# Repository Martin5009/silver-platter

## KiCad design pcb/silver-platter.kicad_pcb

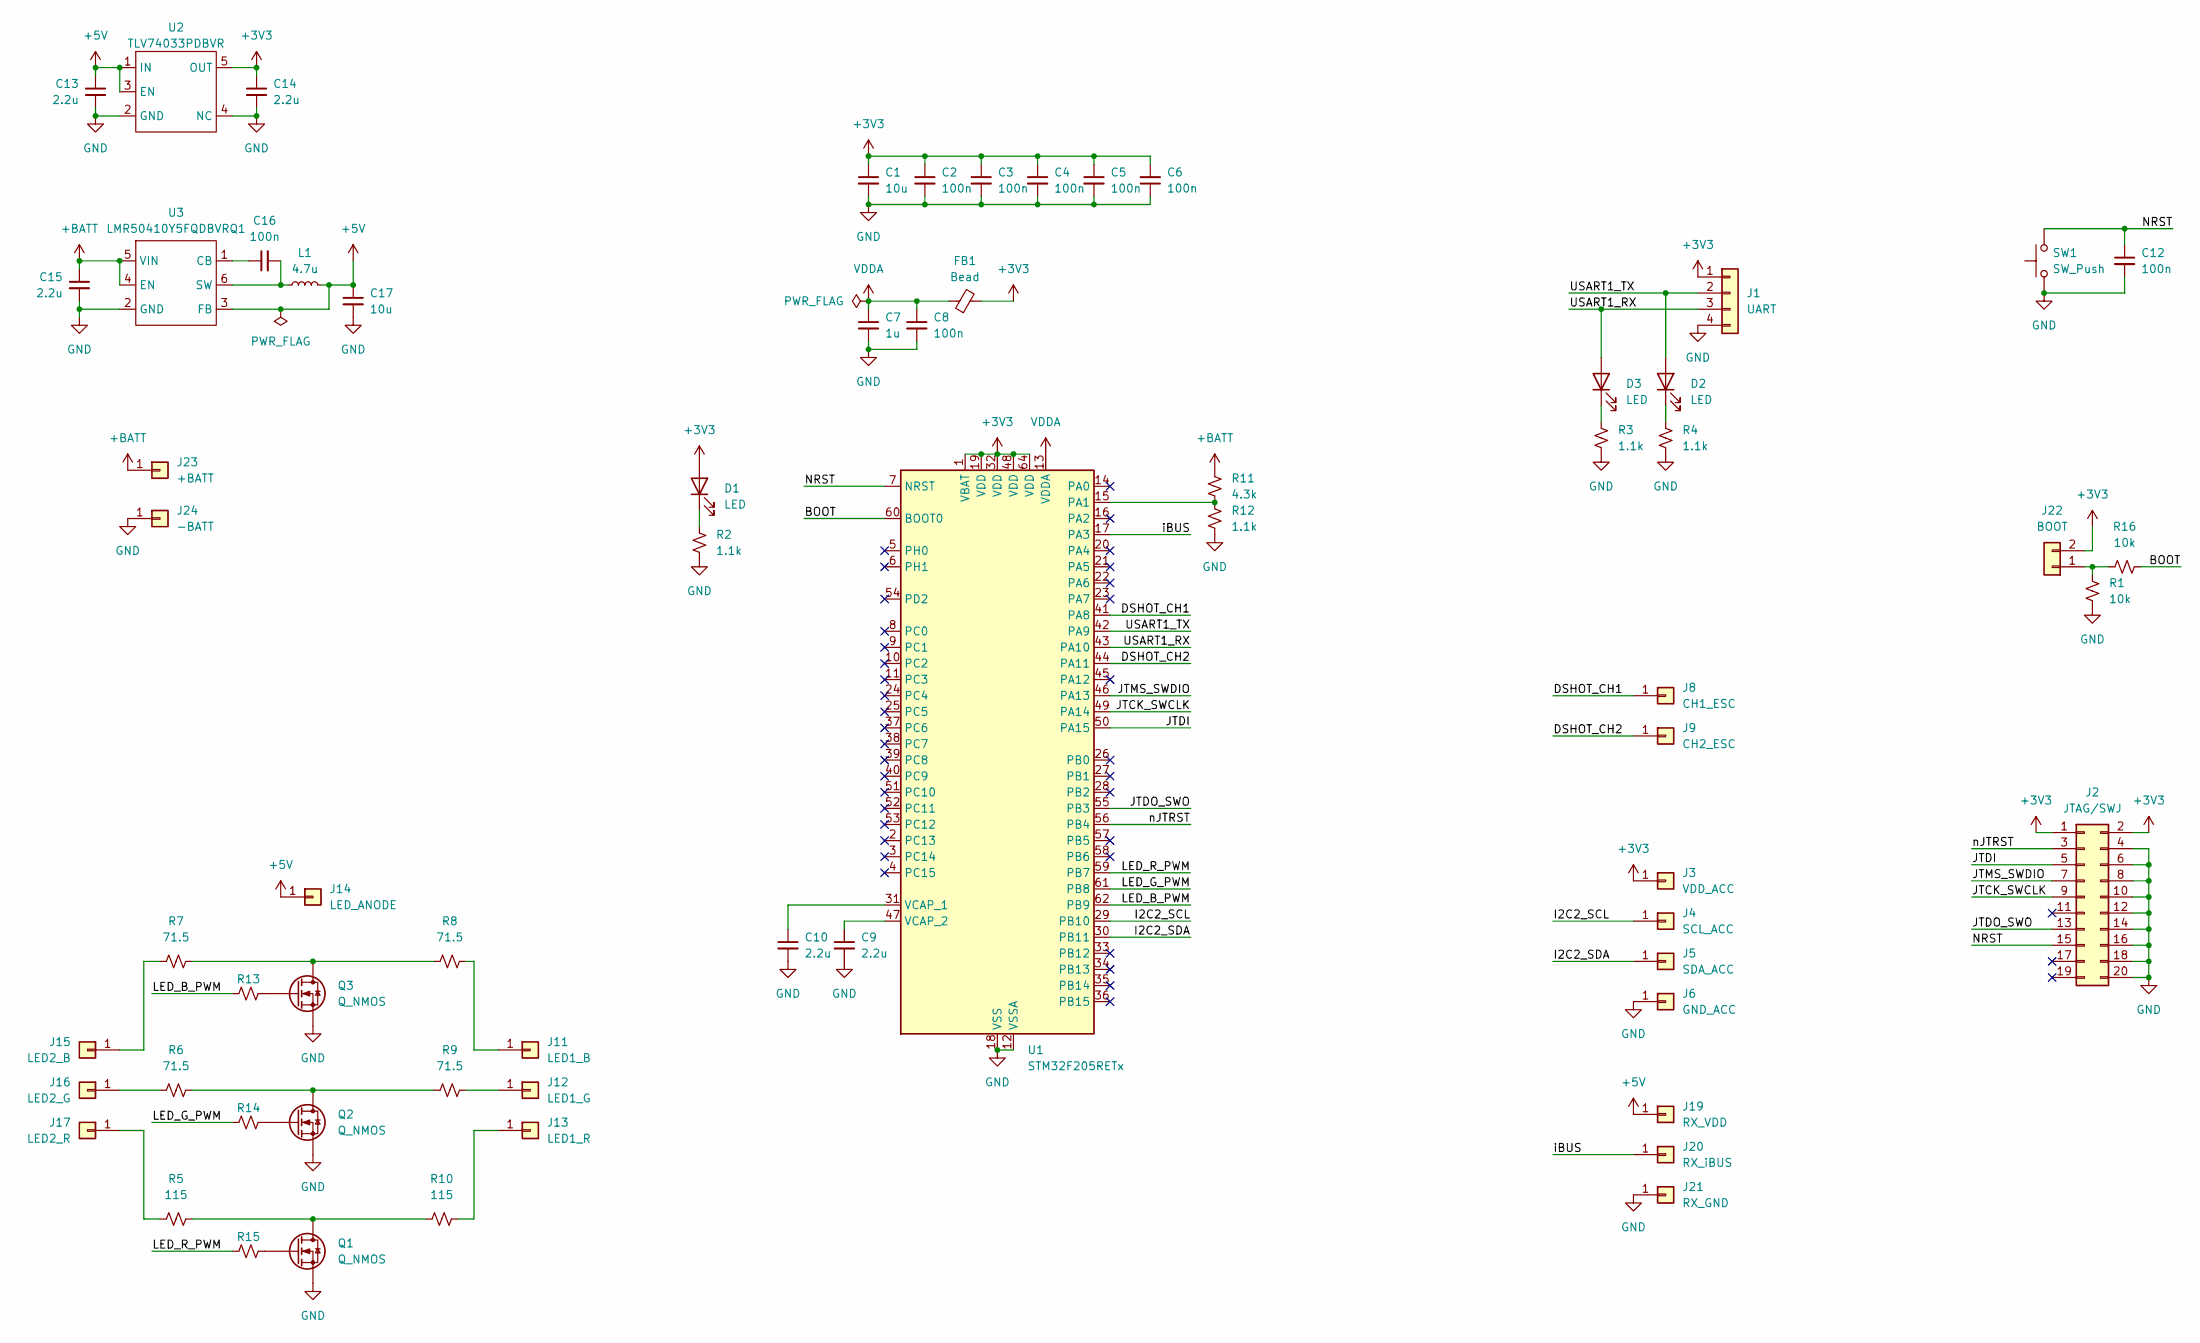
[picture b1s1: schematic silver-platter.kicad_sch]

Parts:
C1, C17: 10u; C_0603_1608Metric_Pad1.08x0.95mm_HandSolder
C2, C3, C4, C5, C6, C8, C12, C16: 100n; C_0603_1608Metric_Pad1.08x0.95mm_HandSolder
C7: 1u; C_0603_1608Metric_Pad1.08x0.95mm_HandSolder
C9, C10, C13, C14, C15: 2.2u; C_0603_1608Metric_Pad1.08x0.95mm_HandSolder
D1, D2, D3: LED; D_0603_1608Metric_Pad1.05x0.95mm_HandSolder
FB1: Bead; L_0603_1608Metric_Pad1.05x0.95mm_HandSolder
J1: UART; PinHeader_1x04_P2.54mm_Vertical
J2: JTAG/SWJ; Wuerth_WR-BHD_61202021621_P2.54mm_Vertical
J3: VDD_ACC; TestPoint_Pad_4.0x4.0mm
J4: SCL_ACC; TestPoint_Pad_4.0x4.0mm
J5: SDA_ACC; TestPoint_Pad_4.0x4.0mm
J6: GND_ACC; TestPoint_Pad_4.0x4.0mm
J8: CH1_ESC; TestPoint_Pad_4.0x4.0mm
J9: CH2_ESC; TestPoint_Pad_4.0x4.0mm
J11: LED1_B; TestPoint_Pad_4.0x4.0mm
J12: LED1_G; TestPoint_Pad_4.0x4.0mm
J13: LED1_R; TestPoint_Pad_4.0x4.0mm
J14: LED_ANODE; TestPoint_Pad_4.0x4.0mm
J15: LED2_B; TestPoint_Pad_4.0x4.0mm
J16: LED2_G; TestPoint_Pad_4.0x4.0mm
J17: LED2_R; TestPoint_Pad_4.0x4.0mm
J19: RX_VDD; TestPoint_Pad_4.0x4.0mm
J20: RX_iBUS; TestPoint_Pad_4.0x4.0mm
J21: RX_GND; TestPoint_Pad_4.0x4.0mm
J22: BOOT; PinHeader_1x02_P2.54mm_Vertical
J23: +BATT; TestPoint_Pad_4.0x4.0mm
J24: -BATT; TestPoint_Pad_4.0x4.0mm
L1: 4.7u; L_1008_2520Metric_Pad1.43x2.20mm_HandSolder
Q1, Q2, Q3: Q_NMOS; SOT-23
R1, R16: 10k; R_0603_1608Metric_Pad0.98x0.95mm_HandSolder
R2, R3, R4, R12: 1.1k; R_0603_1608Metric_Pad0.98x0.95mm_HandSolder
R5, R10: 115; R_0603_1608Metric_Pad0.98x0.95mm_HandSolder
R6, R7, R8, R9: 71.5; R_0603_1608Metric_Pad0.98x0.95mm_HandSolder
R11: 4.3k; R_0603_1608Metric_Pad0.98x0.95mm_HandSolder
R13, R14, R15: R_0603_1608Metric_Pad0.98x0.95mm_HandSolder
SW1: SW_Push; SW_PUSH_6mm
U1: STM32F205RETx; LQFP-64_10x10mm_P0.5mm
U2: TLV74033PDBVR; SOT-23-5
U3: LMR50410Y5FQDBVRQ1; SOT-23-6_Handsoldering

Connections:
+3V3: C1.1, C2.1, C3.1, C4.1, C5.1, C6.2, C14.1, D1.2 (A), FB1.2, J1.1, J2.1, J2.2, J3.1, J22.2, U1.1 (VBAT), U1.19 (VDD), U1.32 (VDD), U1.48 (VDD), U1.64 (VDD), U2.5 (OUT)
+5V: C13.1, C17.1, J14.1, J19.1, L1.2, U2.1 (IN), U2.3 (EN), U3.3 (FB)
+BATT: C15.1, J23.1, R11.2, U3.4 (EN), U3.5 (VIN)
/BOOT: R16.1, U1.60 (BOOT0)
/DSHOT_CH1: J8.1, U1.41 (PA8)
/DSHOT_CH2: J9.1, U1.44 (PA11)
/I2C2_SCL: J4.1, U1.29 (PB10)
/I2C2_SDA: J5.1, U1.30 (PB11)
/JTCK_SWCLK: J2.9, U1.49 (PA14)
/JTDI: J2.5, U1.50 (PA15)
/JTDO_SWO: J2.13, U1.55 (PB3)
/JTMS_SWDIO: J2.7, U1.46 (PA13)
/LED_B_PWM: R13.2, U1.62 (PB9)
/LED_G_PWM: R14.2, U1.61 (PB8)
/LED_R_PWM: R15.2, U1.59 (PB7)
/NRST: C12.1, J2.15, SW1.2, U1.7 (NRST)
/USART1_RX: D3.2 (A), J1.3, U1.43 (PA10)
/USART1_TX: D2.2 (A), J1.2, U1.42 (PA9)
/iBUS: J20.1, U1.17 (PA3)
/nJTRST: J2.3, U1.56 (PB4)
GND: C1.2, C2.2, C3.2, C4.2, C5.2, C6.1, C7.2, C8.2, C9.2, C10.2, C12.2, C13.2, C14.2, C15.2, C17.2, J1.4, J2.4, J2.6, J2.8, J2.10, J2.12, J2.14, J2.16, J2.18, J2.20, J6.1, J21.1, J24.1, Q1.2 (S), Q2.2 (S), Q3.2 (S), R1.1, R2.1, R3.1, R4.1, R12.1, SW1.1, U1.12 (VSSA), U1.18 (VSS), U1.63 (VSS), U2.2 (GND), U2.4 (NC), U3.2 (GND)
unnamed: D1.1 (K), R2.2
unnamed: D2.1 (K), R4.2
unnamed: D3.1 (K), R3.2
unnamed: J11.1, R8.1
unnamed: J12.1, R9.1
unnamed: J13.1, R10.1
unnamed: J15.1, R7.2
unnamed: J16.1, R6.2
unnamed: J17.1, R5.2
unnamed: J22.1, R1.2, R16.2
unnamed: Q1.3 (D), R5.1, R10.2
unnamed: Q1.1 (G), R15.1
unnamed: Q2.3 (D), R6.1, R9.2
unnamed: Q2.1 (G), R14.1
unnamed: Q3.3 (D), R7.1, R8.2
unnamed: Q3.1 (G), R13.1
unnamed: R11.1, R12.2, U1.15 (PA1)
unnamed: C10.1, U1.31 (VCAP_1)
unnamed: C9.1, U1.47 (VCAP_2)
unnamed: C16.1, U3.1 (CB)
unnamed: C16.2, L1.1, U3.6 (SW)
VDDA: C7.1, C8.1, FB1.1, U1.13 (VDDA)

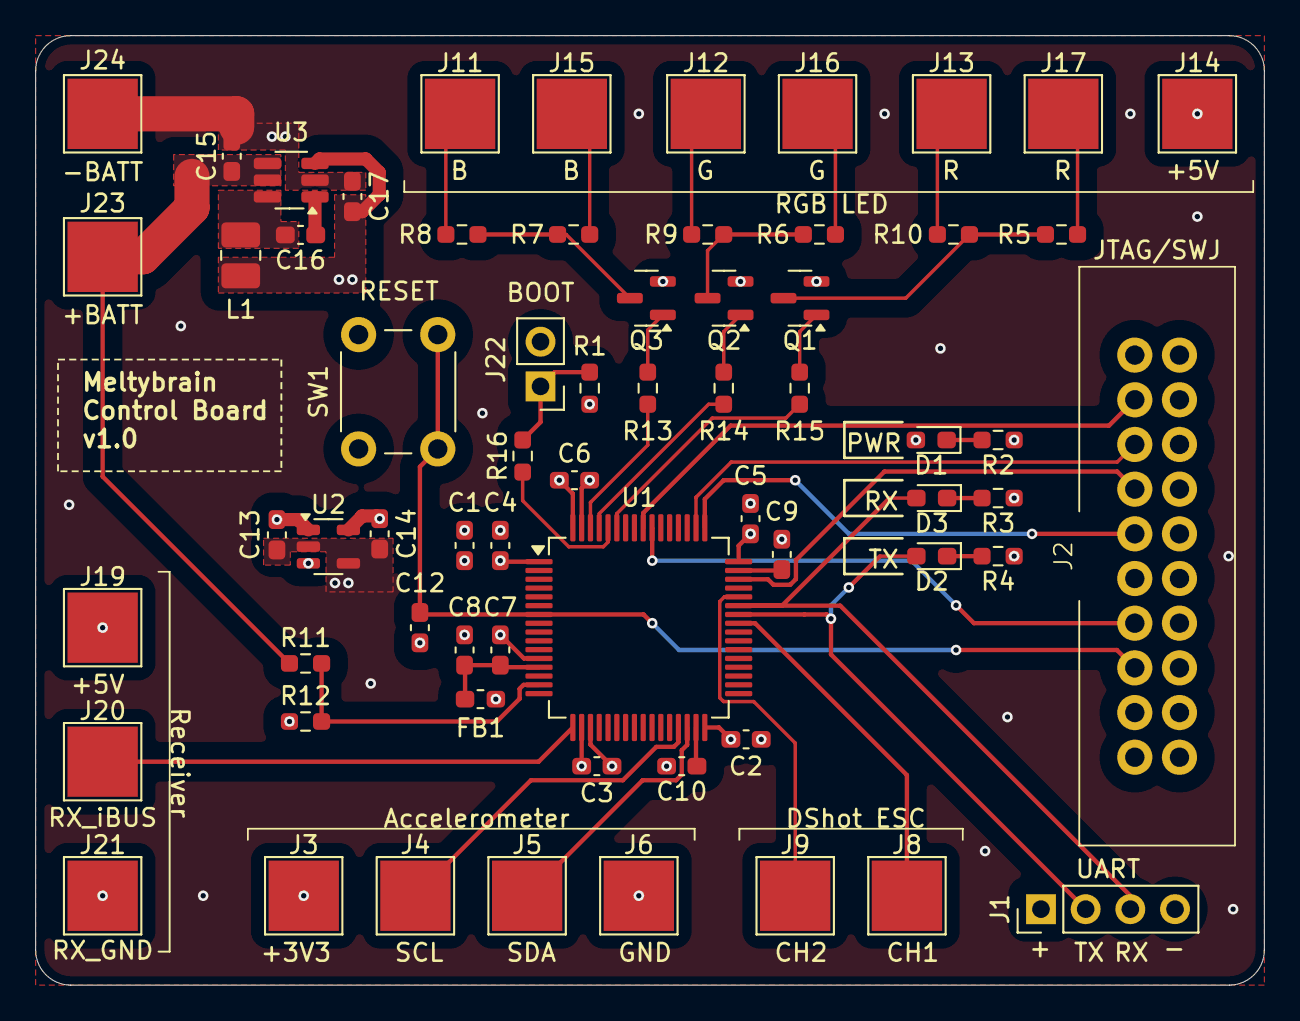
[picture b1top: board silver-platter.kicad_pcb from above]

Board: 4 copper layers, 69.9 x 54.0 mm, 65 parts (0 on the bottom side), 43 nets.

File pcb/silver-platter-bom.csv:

"Id";"Designator";"Footprint";"Quantity";"Designation";"Supplier and ref";
1;"C7";"C_0603_1608Metric_Pad1.08x0.95mm_HandSolder";1;"1u";;;
2;"R4,R3,R12,R2";"R_0603_1608Metric_Pad0.98x0.95mm_HandSolder";4;"1.1k";;;
3;"J16";"TestPoint_Pad_4.0x4.0mm";1;"LED2_G";;;
4;"C17,C1";"C_0603_1608Metric_Pad1.08x0.95mm_HandSolder";2;"10u";;;
5;"J24";"TestPoint_Pad_4.0x4.0mm";1;"-BATT";;;
6;"J12";"TestPoint_Pad_4.0x4.0mm";1;"LED1_G";;;
7;"J14";"TestPoint_Pad_4.0x4.0mm";1;"LED_ANODE";;;
8;"C13,C9,C14,C10,C15";"C_0603_1608Metric_Pad1.08x0.95mm_HandSolder";5;"2.2u";;;
9;"J5";"TestPoint_Pad_4.0x4.0mm";1;"SDA_ACC";;;
10;"J11";"TestPoint_Pad_4.0x4.0mm";1;"LED1_B";;;
11;"J20";"TestPoint_Pad_4.0x4.0mm";1;"RX_iBUS";;;
12;"U2";"SOT-23-5";1;"TLV74033PDBVR";;;
13;"J15";"TestPoint_Pad_4.0x4.0mm";1;"LED2_B";;;
14;"J19";"TestPoint_Pad_4.0x4.0mm";1;"RX_VDD";;;
15;"R1,R16";"R_0603_1608Metric_Pad0.98x0.95mm_HandSolder";2;"10k";;;
16;"R8,R6,R9,R7";"R_0603_1608Metric_Pad0.98x0.95mm_HandSolder";4;"71.5";;;
17;"C8,C2,C6,C16,C3,C12,C4,C5";"C_0603_1608Metric_Pad1.08x0.95mm_HandSolder";8;"100n";;;
18;"J4";"TestPoint_Pad_4.0x4.0mm";1;"SCL_ACC";;;
19;"SW1";"SW_PUSH_6mm";1;"SW_Push";;;
20;"R5,R10";"R_0603_1608Metric_Pad0.98x0.95mm_HandSolder";2;"115";;;
21;"L1";"L_1008_2520Metric_Pad1.43x2.20mm_HandSolder";1;"4.7u";;;
22;"J17";"TestPoint_Pad_4.0x4.0mm";1;"LED2_R";;;
23;"D2,D1,D3";"D_0603_1608Metric_Pad1.05x0.95mm_HandSolder";3;"LED";;;
24;"R13,R15,R14";"R_0603_1608Metric_Pad0.98x0.95mm_HandSolder";3;"~";;;
25;"J2";"Wuerth_WR-BHD_61202021621_P2.54mm_Vertical";1;"JTAG/SWJ";;;
26;"J21";"TestPoint_Pad_4.0x4.0mm";1;"RX_GND";;;
27;"U3";"SOT-23-6_Handsoldering";1;"LMR50410Y5FQDBVRQ1";;;
28;"J3";"TestPoint_Pad_4.0x4.0mm";1;"VDD_ACC";;;
29;"J1";"PinHeader_1x04_P2.54mm_Vertical";1;"UART";;;
30;"J23";"TestPoint_Pad_4.0x4.0mm";1;"+BATT";;;
31;"J6";"TestPoint_Pad_4.0x4.0mm";1;"GND_ACC";;;
32;"Q1,Q3,Q2";"SOT-23";3;"Q_NMOS";;;
33;"J13";"TestPoint_Pad_4.0x4.0mm";1;"LED1_R";;;
34;"J8";"TestPoint_Pad_4.0x4.0mm";1;"CH1_ESC";;;
35;"J9";"TestPoint_Pad_4.0x4.0mm";1;"CH2_ESC";;;
36;"R11";"R_0603_1608Metric_Pad0.98x0.95mm_HandSolder";1;"4.3k";;;
37;"U1";"LQFP-64_10x10mm_P0.5mm";1;"STM32F205RETx";;;
38;"FB1";"L_0603_1608Metric_Pad1.05x0.95mm_HandSolder";1;"Bead";;;
39;"J22";"PinHeader_1x02_P2.54mm_Vertical";1;"BOOT";;;

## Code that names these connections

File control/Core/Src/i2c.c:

/* USER CODE BEGIN Header */
/**
  ******************************************************************************
  * @file    i2c.c
  * @brief   This file provides code for the configuration
  *          of the I2C instances.
  ******************************************************************************
  * @attention
  *
  * Copyright (c) 2025 STMicroelectronics.
  * All rights reserved.
  *
  * This software is licensed under terms that can be found in the LICENSE file
  * in the root directory of this software component.
  * If no LICENSE file comes with this software, it is provided AS-IS.
  *
  ******************************************************************************
  */
/* USER CODE END Header */
/* Includes ------------------------------------------------------------------*/
#include "i2c.h"

/* USER CODE BEGIN 0 */

/* USER CODE END 0 */

I2C_HandleTypeDef hi2c2;

/* I2C2 init function */
void MX_I2C2_Init(void)
{

  /* USER CODE BEGIN I2C2_Init 0 */

  /* USER CODE END I2C2_Init 0 */

  /* USER CODE BEGIN I2C2_Init 1 */

  /* USER CODE END I2C2_Init 1 */
  hi2c2.Instance = I2C2;
  hi2c2.Init.ClockSpeed = 100000;
  hi2c2.Init.DutyCycle = I2C_DUTYCYCLE_2;
  hi2c2.Init.OwnAddress1 = 166;
  hi2c2.Init.AddressingMode = I2C_ADDRESSINGMODE_7BIT;
  hi2c2.Init.DualAddressMode = I2C_DUALADDRESS_DISABLE;
  hi2c2.Init.OwnAddress2 = 0;
  hi2c2.Init.GeneralCallMode = I2C_GENERALCALL_DISABLE;
  hi2c2.Init.NoStretchMode = I2C_NOSTRETCH_DISABLE;
  if (HAL_I2C_Init(&hi2c2) != HAL_OK)
  {
    Error_Handler();
  }
  /* USER CODE BEGIN I2C2_Init 2 */

  /* USER CODE END I2C2_Init 2 */

}

void HAL_I2C_MspInit(I2C_HandleTypeDef* i2cHandle)
{

  GPIO_InitTypeDef GPIO_InitStruct = {0};
  if(i2cHandle->Instance==I2C2)
  {
  /* USER CODE BEGIN I2C2_MspInit 0 */

  /* USER CODE END I2C2_MspInit 0 */

    __HAL_RCC_GPIOB_CLK_ENABLE();
    /**I2C2 GPIO Configuration
    PB10     ------> I2C2_SCL
    PB11     ------> I2C2_SDA
    */
    GPIO_InitStruct.Pin = GPIO_PIN_10|GPIO_PIN_11;
    GPIO_InitStruct.Mode = GPIO_MODE_AF_OD;
    GPIO_InitStruct.Pull = GPIO_NOPULL;
    GPIO_InitStruct.Speed = GPIO_SPEED_FREQ_VERY_HIGH;
    GPIO_InitStruct.Alternate = GPIO_AF4_I2C2;
    HAL_GPIO_Init(GPIOB, &GPIO_InitStruct);

    /* I2C2 clock enable */
    __HAL_RCC_I2C2_CLK_ENABLE();

    /* I2C2 interrupt Init */
    HAL_NVIC_SetPriority(I2C2_EV_IRQn, 0, 0);
    HAL_NVIC_EnableIRQ(I2C2_EV_IRQn);
  /* USER CODE BEGIN I2C2_MspInit 1 */

  /* USER CODE END I2C2_MspInit 1 */
  }
}

void HAL_I2C_MspDeInit(I2C_HandleTypeDef* i2cHandle)
{

  if(i2cHandle->Instance==I2C2)
  {
  /* USER CODE BEGIN I2C2_MspDeInit 0 */

  /* USER CODE END I2C2_MspDeInit 0 */
    /* Peripheral clock disable */
    __HAL_RCC_I2C2_CLK_DISABLE();

    /**I2C2 GPIO Configuration
    PB10     ------> I2C2_SCL
    PB11     ------> I2C2_SDA
    */
    HAL_GPIO_DeInit(GPIOB, GPIO_PIN_10);

    HAL_GPIO_DeInit(GPIOB, GPIO_PIN_11);

    /* I2C2 interrupt Deinit */
    HAL_NVIC_DisableIRQ(I2C2_EV_IRQn);
  /* USER CODE BEGIN I2C2_MspDeInit 1 */

  /* USER CODE END I2C2_MspDeInit 1 */
  }
}

/* USER CODE BEGIN 1 */

/* USER CODE END 1 */

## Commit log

2025-07-02 LED drive circuit added to schematic
2025-07-06 Schematic Draft 1
2025-07-06 Layout draft 1
2025-07-06 Silkscreen
2025-07-06 Gerbers
2025-07-07 Indicator LED resistors from 1.1k to 4.3k
2025-11-23 Added control board source code
2025-11-23 pcb files
